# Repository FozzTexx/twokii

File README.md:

This is a program to emulate a PS/2 keyboard and PS/2 mouse so that a
Raspberry Pi can act as the keyboard and mouse of another
computer. Mostly for use with a video capture device so that a
Raspberry Pi can act as a IP KVM.

There is no video capture stuff here, this is **only** PS/2 keyboard &
mouse emulation.

This also does not allow you to connect a PS/2 keyoard or mouse *to* a
Raspberry Pi, it lets the Pi be the keyboard and mouse. This feature
may be included in a future version though.

fozztexx@fozztexx.com

---

See COPYING file for detailed information on terms of copying.

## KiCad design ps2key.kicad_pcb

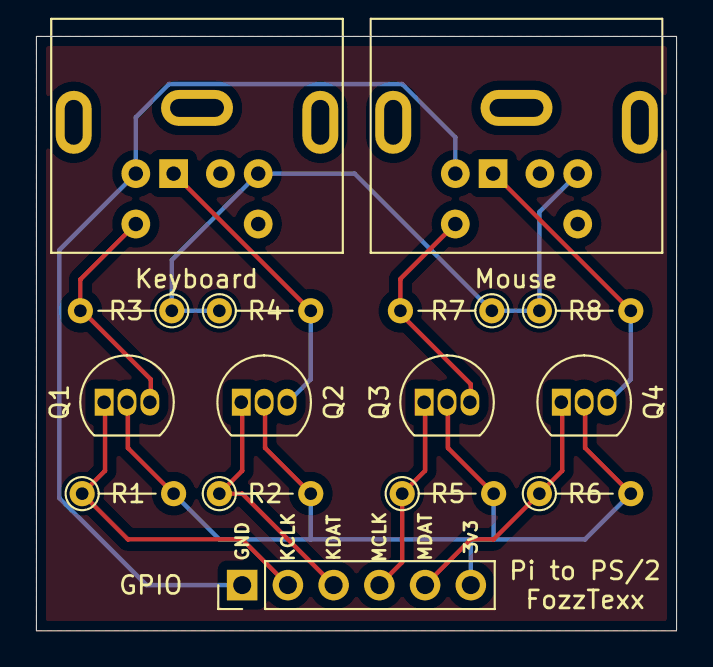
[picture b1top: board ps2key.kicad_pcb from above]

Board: 2 copper layers, 35.6 x 33.0 mm, 15 parts (0 on the bottom side), 11 nets.

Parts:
GPIO: GPIO; PinHeader_1x06_P2.54mm_Vertical
Keyboard: Keyboard; Connector_Mini-DIN_Female_6Pin_2rows
Mouse: Mouse; Connector_Mini-DIN_Female_6Pin_2rows
Q1, Q2, Q3, Q4: 2N7000; TO-92_Inline
R1, R2, R3, R4, R5, R6, R7, R8: 10k; R_Axial_DIN0204_L3.6mm_D1.6mm_P5.08mm_Vertical

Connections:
/3v3: GPIO.6, Q1.2, Q2.2, Q3.2, Q4.2, R1.2, R2.2, R5.2, R6.2
/5V: Keyboard.4, Mouse.4, R3.1, R4.1, R7.1, R8.1
/CLK_K: GPIO.2, Q1.1, R1.1
/CLK_M: GPIO.4, Q3.1, R5.1
/DATA_K: GPIO.3, Q2.1, R2.1
/DATA_M: GPIO.5, Q4.1, R6.1
/GND: GPIO.1, Keyboard.3, Mouse.3
/KBDCLK: Keyboard.1, Q2.3, R4.2
/KBDDATA: Keyboard.5, Q1.3, R3.2
/MOUCLK: Mouse.1, Q4.3, R8.2
/MOUDATA: Mouse.5, Q3.3, R7.2

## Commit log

2020-08-23 Initial version.
2020-08-24 Split ps2 functions into their own file.
2020-08-28 Make sure host is really trying to send data before aborting.
2020-09-22 Added mouse support.
2021-04-22 Try to improve PS/2 compatibility.
2021-04-22 Added license and README.
2021-04-23 Added circuit.
